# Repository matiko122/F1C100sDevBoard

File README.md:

# F1C100sDevBoard
Yet another Embedded Linux board for training purposes. Interactive BOM can be found in the directory ./F1C100s/bom

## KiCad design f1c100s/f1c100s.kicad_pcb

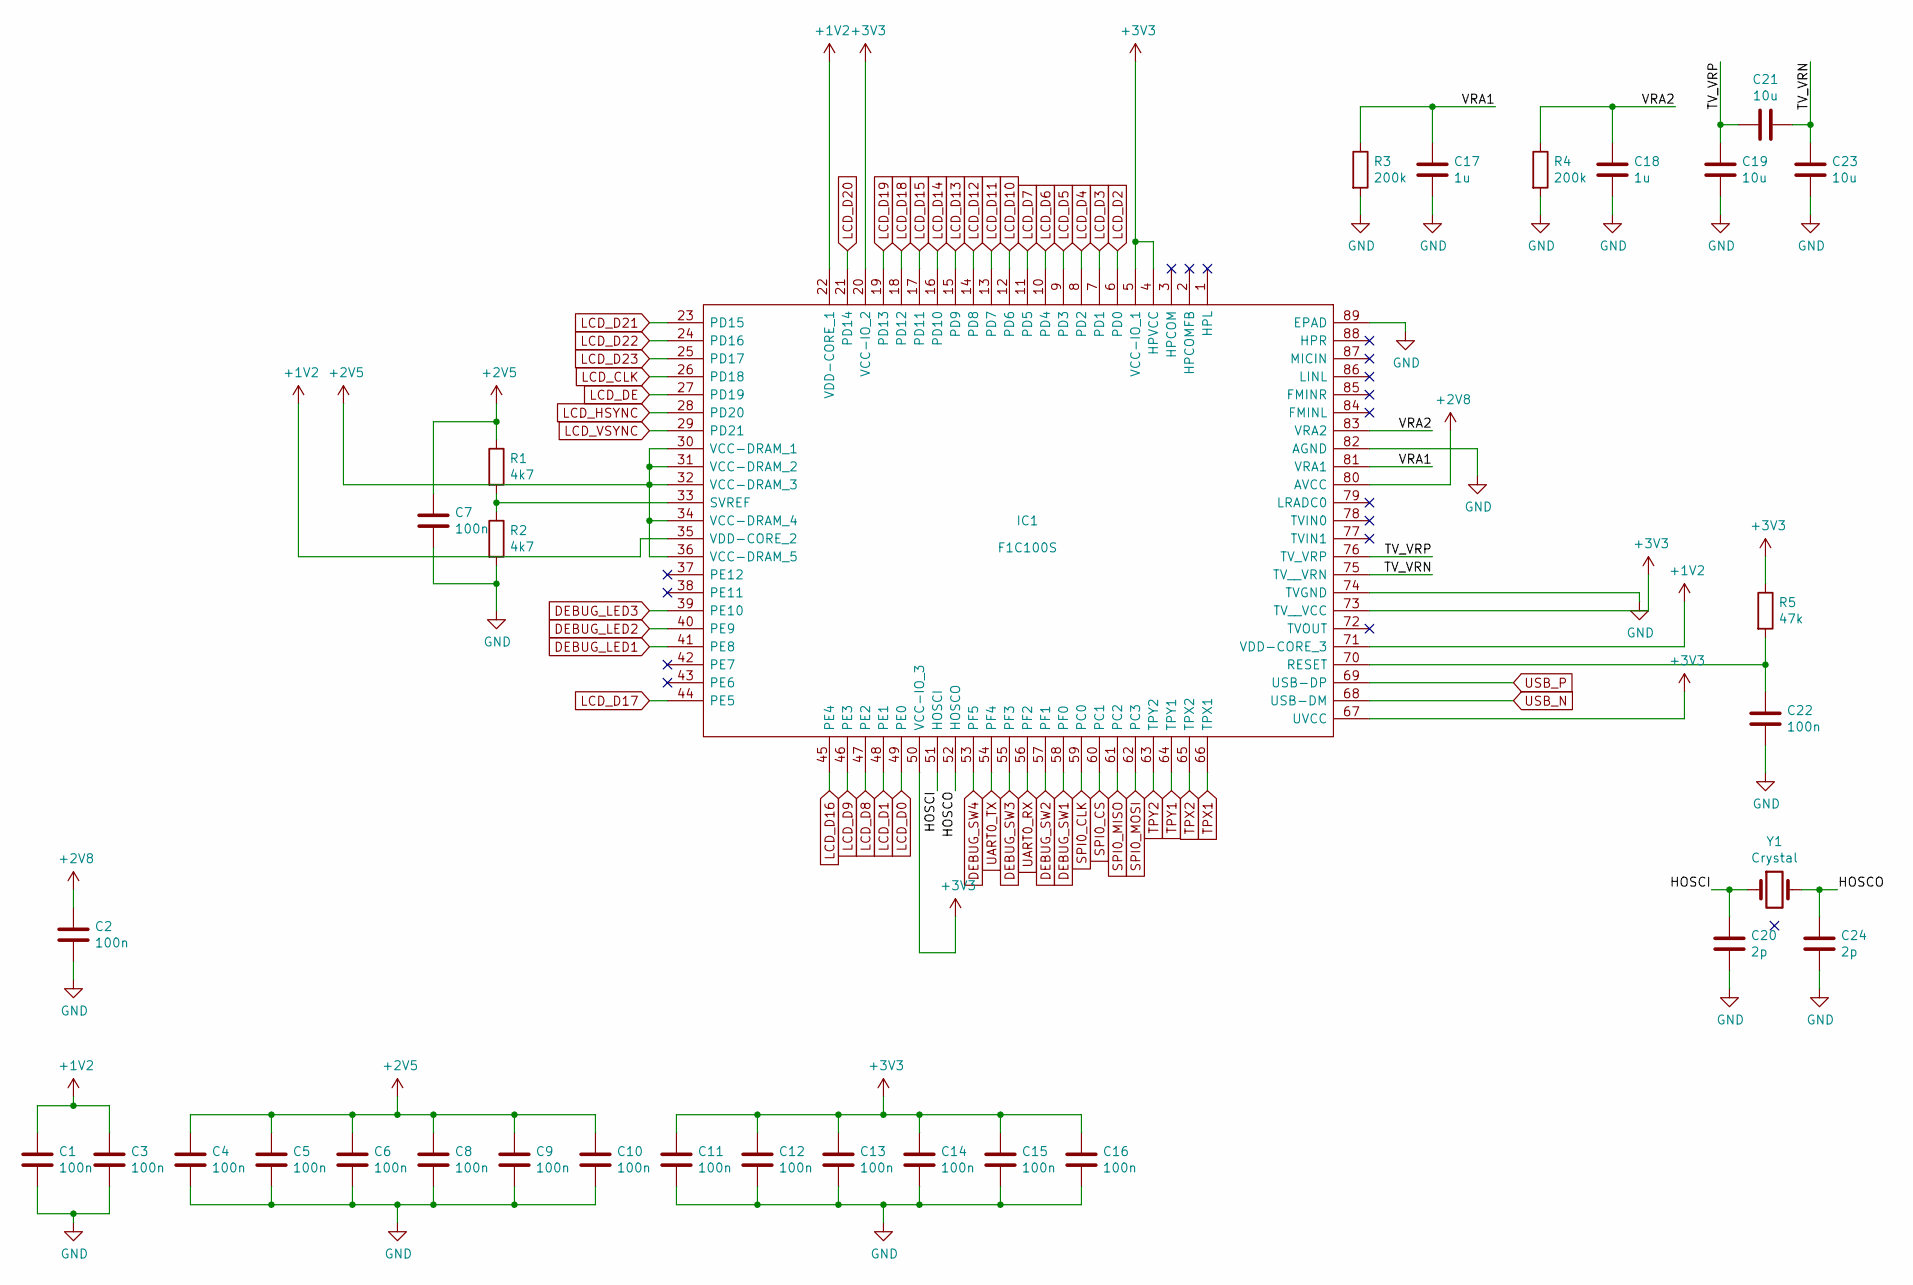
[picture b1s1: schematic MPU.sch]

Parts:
C1, C2, C3, C4, C5, C6, C7, C8, C9, C10, C11, C12, C13, C14, C15, C16, C22: 100n; C_0402_1005Metric_Pad0.74x0.62mm_HandSolder
C17, C18: 1u; C_0402_1005Metric_Pad0.74x0.62mm_HandSolder
C19, C21, C23: 10u; C_0402_1005Metric_Pad0.74x0.62mm_HandSolder
C20, C24: 2p; C_0402_1005Metric_Pad0.74x0.62mm_HandSolder
IC1: F1C100S; QFN40P1000X1000X90-89N-D; Manufacturer_Part_Number F1C100S
R1, R2: 4k7; R_0402_1005Metric_Pad0.72x0.64mm_HandSolder
R3, R4: 200k; R_0402_1005Metric_Pad0.72x0.64mm_HandSolder
R5: 47k; R_0402_1005Metric_Pad0.72x0.64mm_HandSolder
Y1: Crystal; LFXTAL036533

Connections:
+1V2: C1.1, C3.1, IC1.22 (VDD-CORE_1), IC1.35 (VDD-CORE_2), IC1.71 (VDD-CORE_3); also elsewhere on the board
+2V5: C4.1, C5.1, C6.1, C7.1, C8.1, C9.1, C10.1, IC1.30 (VCC-DRAM_1), IC1.31 (VCC-DRAM_2), IC1.32 (VCC-DRAM_3), IC1.34 (VCC-DRAM_4), IC1.36 (VCC-DRAM_5), R1.1; also elsewhere on the board
+2V8: C2.1, IC1.80 (AVCC); also elsewhere on the board
+3V3: C11.1, C12.1, C13.1, C14.1, C15.1, C16.1, IC1.4 (HPVCC), IC1.5 (VCC-IO_1), IC1.20 (VCC-IO_2), IC1.50 (VCC-IO_3), IC1.67 (UVCC), IC1.73 (TV__VCC), R5.1; also elsewhere on the board
/MPU/HOSCI: C20.1, IC1.51 (HOSCI), Y1.1
/MPU/HOSCO: C24.1, IC1.52 (HOSCO), Y1.2
/MPU/TV_VRN: C21.1, C23.2, IC1.75 (TV__VRN)
/MPU/TV_VRP: C19.2, C21.2, IC1.76 (TV_VRP)
/MPU/VRA1: C17.1, IC1.81 (VRA1), R3.1
/MPU/VRA2: C18.1, IC1.83 (VRA2), R4.1
DEBUG_LED1: IC1.41 (PE8); also elsewhere on the board
DEBUG_LED2: IC1.40 (PE9); also elsewhere on the board
DEBUG_LED3: IC1.39 (PE10); also elsewhere on the board
DEBUG_SW1: IC1.58 (PF0); also elsewhere on the board
DEBUG_SW2: IC1.57 (PF1); also elsewhere on the board
DEBUG_SW3: IC1.55 (PF3); also elsewhere on the board
DEBUG_SW4: IC1.53 (PF5); also elsewhere on the board
GND: C1.2, C2.2, C3.2, C4.2, C5.2, C6.2, C7.2, C8.2, C9.2, C10.2, C11.2, C12.2, C13.2, C14.2, C15.2, C16.2, C17.2, C18.2, C19.1, C20.2, C22.2, C23.1, C24.2, IC1.74 (TVGND), IC1.82 (AGND), IC1.89 (EPAD), R2.2, R3.2, R4.2; also elsewhere on the board
LCD_CLK: IC1.26 (PD18); also elsewhere on the board
LCD_D0: IC1.49 (PE0); also elsewhere on the board
LCD_D1: IC1.48 (PE1); also elsewhere on the board
LCD_D2: IC1.6 (PD0); also elsewhere on the board
LCD_D3: IC1.7 (PD1); also elsewhere on the board
LCD_D4: IC1.8 (PD2); also elsewhere on the board
LCD_D5: IC1.9 (PD3); also elsewhere on the board
LCD_D6: IC1.10 (PD4); also elsewhere on the board
LCD_D7: IC1.11 (PD5); also elsewhere on the board
LCD_D8: IC1.47 (PE2); also elsewhere on the board
LCD_D9: IC1.46 (PE3); also elsewhere on the board
LCD_D10: IC1.12 (PD6); also elsewhere on the board
LCD_D11: IC1.13 (PD7); also elsewhere on the board
LCD_D12: IC1.14 (PD8); also elsewhere on the board
LCD_D13: IC1.15 (PD9); also elsewhere on the board
LCD_D14: IC1.16 (PD10); also elsewhere on the board
LCD_D15: IC1.17 (PD11); also elsewhere on the board
LCD_D16: IC1.45 (PE4); also elsewhere on the board
LCD_D17: IC1.44 (PE5); also elsewhere on the board
LCD_D18: IC1.18 (PD12); also elsewhere on the board
LCD_D19: IC1.19 (PD13); also elsewhere on the board
LCD_D20: IC1.21 (PD14); also elsewhere on the board
LCD_D21: IC1.23 (PD15); also elsewhere on the board
LCD_D22: IC1.24 (PD16); also elsewhere on the board
LCD_D23: IC1.25 (PD17); also elsewhere on the board
LCD_DE: IC1.27 (PD19); also elsewhere on the board
LCD_HSYNC: IC1.28 (PD20); also elsewhere on the board
LCD_VSYNC: IC1.29 (PD21); also elsewhere on the board
unnamed: C22.1, IC1.70 (RESET), R5.2
unnamed: IC1.33 (SVREF), R1.2, R2.1
SPI0_CLK: IC1.59 (PC0); also elsewhere on the board
SPI0_CS: IC1.60 (PC1); also elsewhere on the board
SPI0_MISO: IC1.61 (PC2); also elsewhere on the board
SPI0_MOSI: IC1.62 (PC3); also elsewhere on the board
TPX1: IC1.66 (TPX1); also elsewhere on the board
TPX2: IC1.65 (TPX2); also elsewhere on the board
TPY1: IC1.64 (TPY1); also elsewhere on the board
TPY2: IC1.63 (TPY2); also elsewhere on the board
UART0_RX: IC1.56 (PF2); also elsewhere on the board
UART0_TX: IC1.54 (PF4); also elsewhere on the board
USB_N: IC1.68 (USB-DM); also elsewhere on the board
USB_P: IC1.69 (USB-DP); also elsewhere on the board

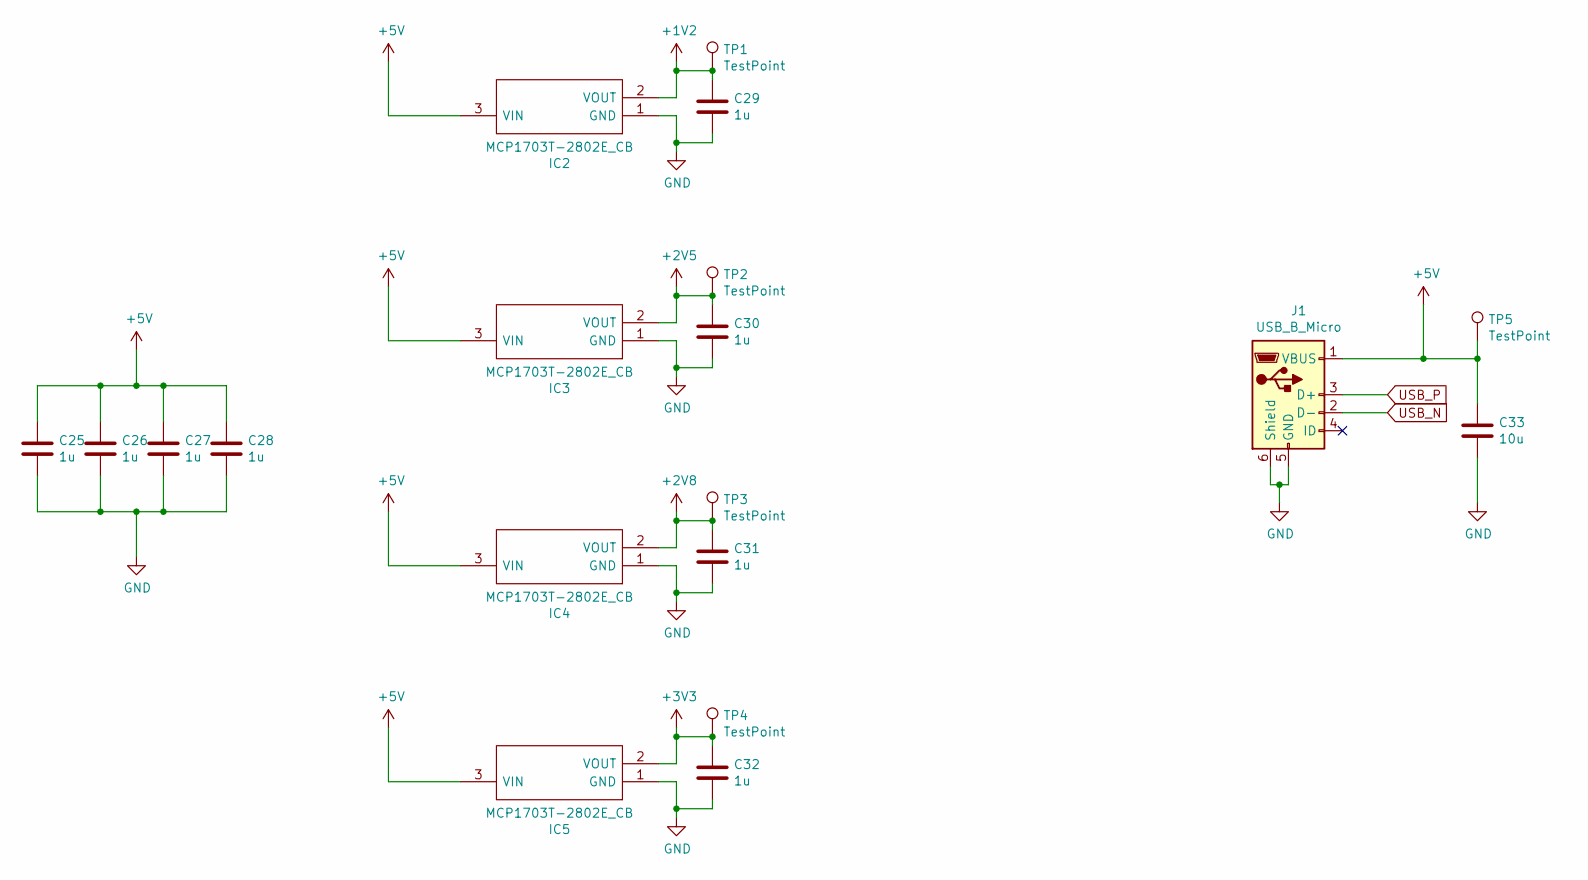
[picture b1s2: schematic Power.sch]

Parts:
C25, C26, C27, C28, C29, C30, C31, C32: 1u; C_0402_1005Metric_Pad0.74x0.62mm_HandSolder
C33: 10u; C_0402_1005Metric_Pad0.74x0.62mm_HandSolder
IC2, IC3, IC4, IC5: MCP1703T-2802E_CB; SOT95P255X145-3N; Manufacturer_Part_Number MCP1703T-2802E/CB; Mouser Part Number 579-MCP1703T2802E/CB
J1: USB_B_Micro; USB_Micro-B_Amphenol_10118194_Horizontal
TP1, TP2, TP3, TP4, TP5: TestPoint; TestPoint_Pad_2.0x2.0mm

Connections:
+1V2: C29.1, IC2.2 (VOUT), TP1.1; also elsewhere on the board
+2V5: C30.1, IC3.2 (VOUT), TP2.1; also elsewhere on the board
+2V8: C31.1, IC4.2 (VOUT), TP3.1; also elsewhere on the board
+3V3: C32.1, IC5.2 (VOUT), TP4.1; also elsewhere on the board
+5V: C25.1, C26.1, C27.1, C28.1, C33.1, IC2.3 (VIN), IC3.3 (VIN), IC4.3 (VIN), IC5.3 (VIN), J1.1 (VBUS), TP5.1; also elsewhere on the board
GND: C25.2, C26.2, C27.2, C28.2, C29.2, C30.2, C31.2, C32.2, C33.2, IC2.1 (GND), IC3.1 (GND), IC4.1 (GND), IC5.1 (GND), J1.5 (GND), J1.6 (Shield); also elsewhere on the board
USB_N: J1.2 (D-); also elsewhere on the board
USB_P: J1.3 (D+); also elsewhere on the board

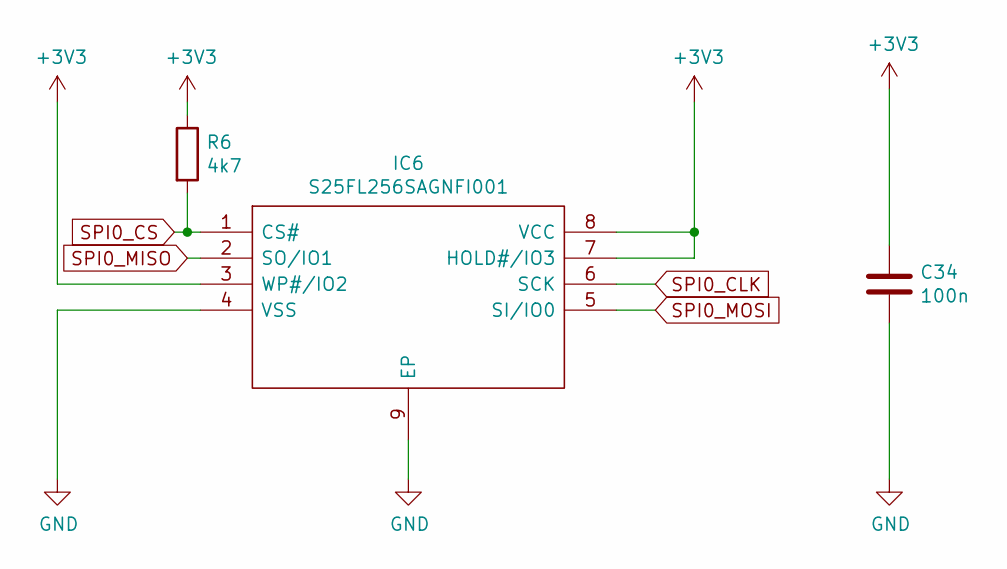
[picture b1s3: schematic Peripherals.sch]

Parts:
C34: 100n; C_0402_1005Metric_Pad0.74x0.62mm_HandSolder
IC6: S25FL256SAGNFI001; SON127P800X600X80-9N-D; Manufacturer_Part_Number S25FL256SAGNFI001
R6: 4k7; R_0402_1005Metric_Pad0.72x0.64mm_HandSolder

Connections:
+3V3: C34.1, IC6.3 (WP#/IO2), IC6.7 (HOLD#/IO3), IC6.8 (VCC), R6.1; also elsewhere on the board
GND: C34.2, IC6.4 (VSS), IC6.9 (EP); also elsewhere on the board
SPI0_CLK: IC6.6 (SCK); also elsewhere on the board
SPI0_CS: IC6.1 (CS#), R6.2; also elsewhere on the board
SPI0_MISO: IC6.2 (SO/IO1); also elsewhere on the board
SPI0_MOSI: IC6.5 (SI/IO0); also elsewhere on the board

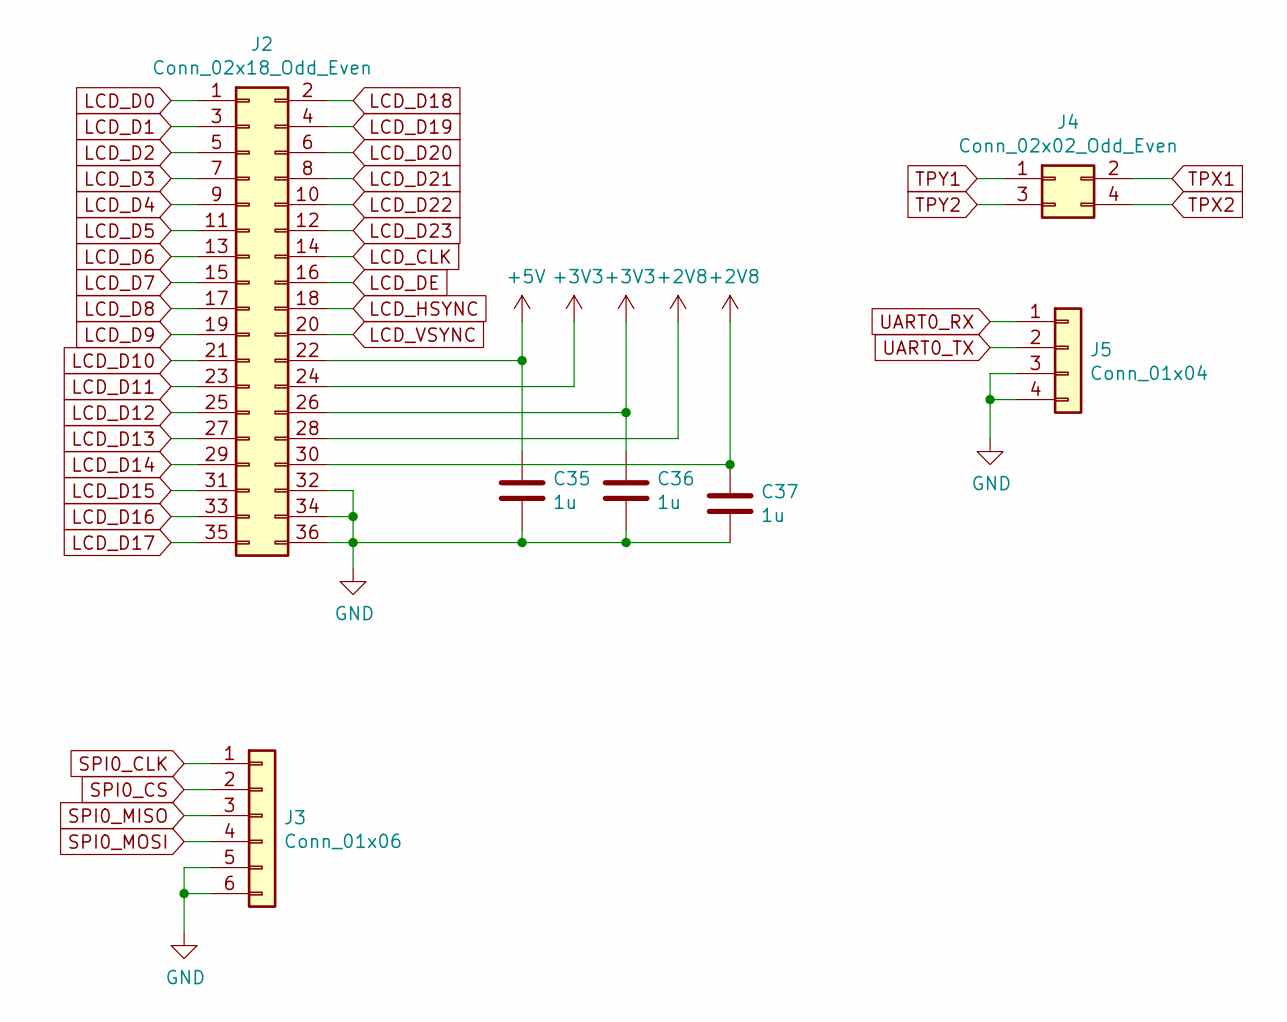
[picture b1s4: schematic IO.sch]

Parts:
C35, C36, C37: 1u; C_0402_1005Metric_Pad0.74x0.62mm_HandSolder
J2: Conn_02x18_Odd_Even; PinHeader_2x18_P2.54mm_Vertical
J3: Conn_01x06; PinHeader_1x06_P2.54mm_Vertical
J4: Conn_02x02_Odd_Even; PinHeader_2x02_P2.54mm_Vertical
J5: Conn_01x04; PinHeader_1x04_P2.54mm_Vertical

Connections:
+2V8: C37.1, J2.28, J2.30; also elsewhere on the board
+3V3: C36.1, J2.24, J2.26; also elsewhere on the board
+5V: C35.1, J2.22; also elsewhere on the board
GND: C35.2, C36.2, C37.2, J2.32, J2.34, J2.36, J3.5, J3.6, J5.3, J5.4; also elsewhere on the board
LCD_CLK: J2.14; also elsewhere on the board
LCD_D0: J2.1; also elsewhere on the board
LCD_D1: J2.3; also elsewhere on the board
LCD_D2: J2.5; also elsewhere on the board
LCD_D3: J2.7; also elsewhere on the board
LCD_D4: J2.9; also elsewhere on the board
LCD_D5: J2.11; also elsewhere on the board
LCD_D6: J2.13; also elsewhere on the board
LCD_D7: J2.15; also elsewhere on the board
LCD_D8: J2.17; also elsewhere on the board
LCD_D9: J2.19; also elsewhere on the board
LCD_D10: J2.21; also elsewhere on the board
LCD_D11: J2.23; also elsewhere on the board
LCD_D12: J2.25; also elsewhere on the board
LCD_D13: J2.27; also elsewhere on the board
LCD_D14: J2.29; also elsewhere on the board
LCD_D15: J2.31; also elsewhere on the board
LCD_D16: J2.33; also elsewhere on the board
LCD_D17: J2.35; also elsewhere on the board
LCD_D18: J2.2; also elsewhere on the board
LCD_D19: J2.4; also elsewhere on the board
LCD_D20: J2.6; also elsewhere on the board
LCD_D21: J2.8; also elsewhere on the board
LCD_D22: J2.10; also elsewhere on the board
LCD_D23: J2.12; also elsewhere on the board
LCD_DE: J2.16; also elsewhere on the board
LCD_HSYNC: J2.18; also elsewhere on the board
LCD_VSYNC: J2.20; also elsewhere on the board
SPI0_CLK: J3.1; also elsewhere on the board
SPI0_CS: J3.2; also elsewhere on the board
SPI0_MISO: J3.3; also elsewhere on the board
SPI0_MOSI: J3.4; also elsewhere on the board
TPX1: J4.2; also elsewhere on the board
TPX2: J4.4; also elsewhere on the board
TPY1: J4.1; also elsewhere on the board
TPY2: J4.3; also elsewhere on the board
UART0_RX: J5.1; also elsewhere on the board
UART0_TX: J5.2; also elsewhere on the board

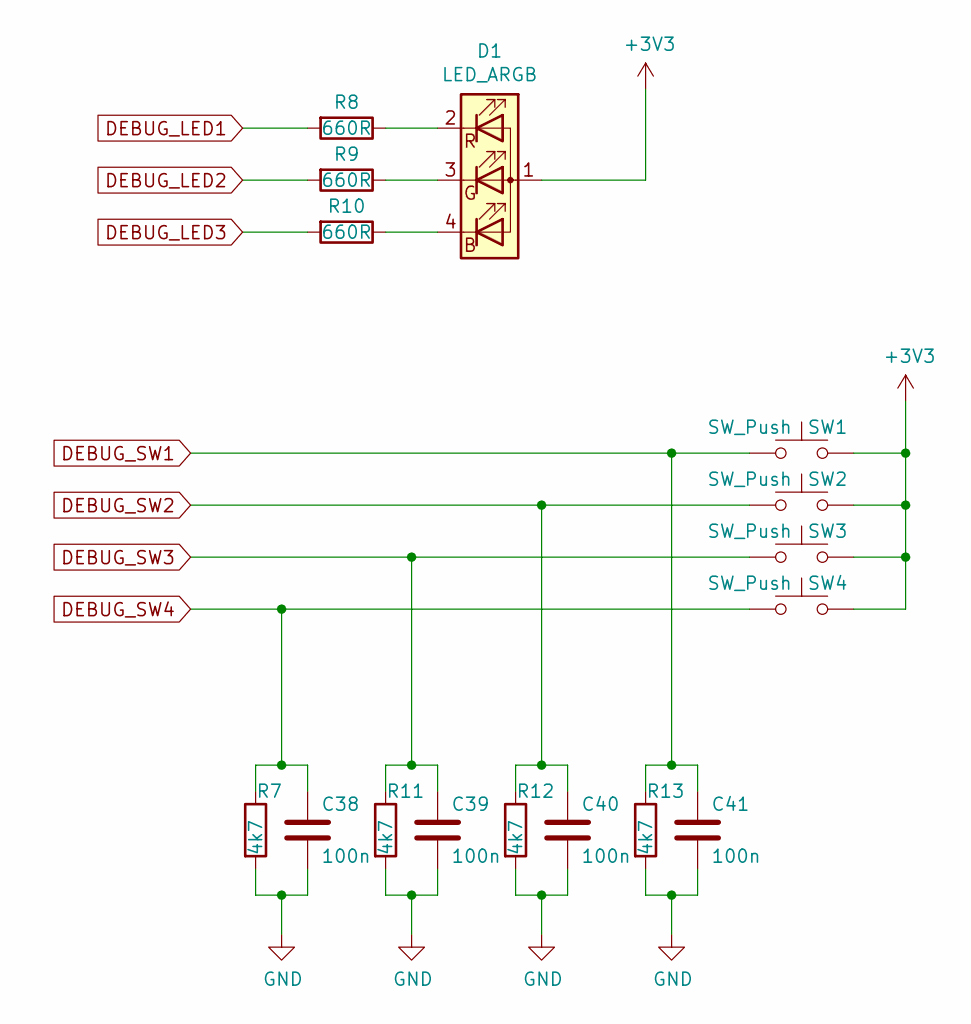
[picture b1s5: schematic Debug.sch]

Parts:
C38, C39, C40, C41: 100n; C_0402_1005Metric_Pad0.74x0.62mm_HandSolder
D1: LED_ARGB; SOIC-4
R7, R11, R12, R13: 4k7; R_0402_1005Metric_Pad0.72x0.64mm_HandSolder
R8, R9, R10: 660R; R_0402_1005Metric_Pad0.72x0.64mm_HandSolder
SW1, SW2, SW3, SW4: SW_Push; CK-SWITCH_G

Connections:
+3V3: D1.1 (A), SW1.2, SW2.2, SW3.2, SW4.2; also elsewhere on the board
DEBUG_LED1: R8.2; also elsewhere on the board
DEBUG_LED2: R9.2; also elsewhere on the board
DEBUG_LED3: R10.2; also elsewhere on the board
DEBUG_SW1: C41.1, R13.1, SW1.1; also elsewhere on the board
DEBUG_SW2: C40.1, R12.1, SW2.1; also elsewhere on the board
DEBUG_SW3: C39.1, R11.1, SW3.1; also elsewhere on the board
DEBUG_SW4: C38.1, R7.1, SW4.1; also elsewhere on the board
GND: C38.2, C39.2, C40.2, C41.2, R7.2, R11.2, R12.2, R13.2; also elsewhere on the board
unnamed: D1.2 (RK), R8.1
unnamed: D1.3 (GK), R9.1
unnamed: D1.4 (BK), R10.1

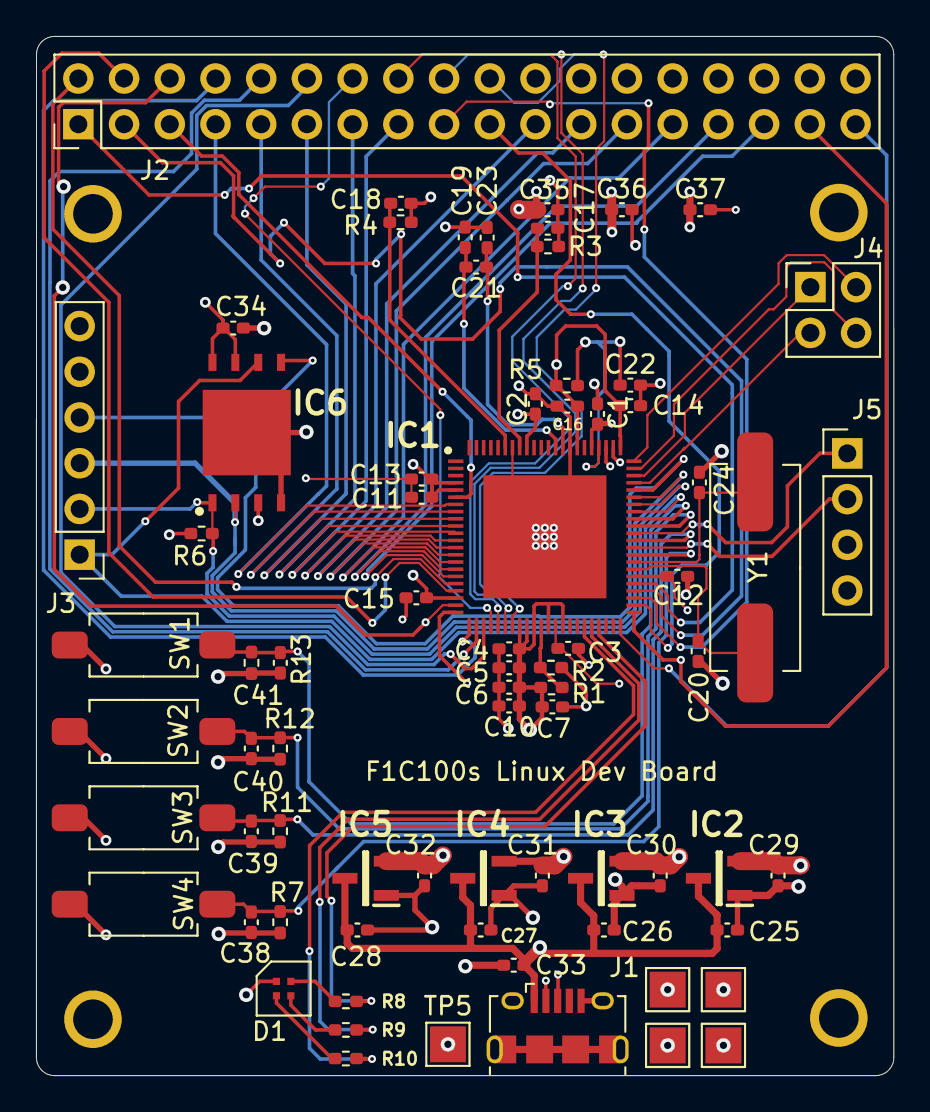
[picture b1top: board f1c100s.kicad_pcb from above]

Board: 4 copper layers, 47.6 x 57.7 mm, 74 parts (0 on the bottom side), 64 nets.

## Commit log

2020-10-14 Schematic created. Basic board shape created (to fix: create mounting holes). Some traces laid down.
2020-10-27 Work in progress...
2020-10-27 Sadly I have to use a little bit more of GND
2020-10-27 Almost ready
2020-10-27 All done i guess. DRC a little bit fuzzy but whatever.
2020-10-27 Production files generated.
2020-10-27 Now generated.
2020-11-08 Production files ready!
2021-04-25 Added interactive bom and render
